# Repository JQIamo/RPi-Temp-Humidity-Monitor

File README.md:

# RPi-Temp-Humidity-Monitor
Raspberry-Pi driven temperature and humidity sensing via DHT22.

Short-URL: http://git.io/vRFkn

## Ordering Boards:
v1.1 Boards are orderable from OSHPark at the following links:

- [PiTempLoggerv1.1-PiSide](https://oshpark.com/shared_projects/A5WHpdao) @ $34.50 per 3 boards
- [PiTempLoggerv1.1-Sensor](https://oshpark.com/shared_projects/NIQoCTse) @ $12.00 per 3 boards

They have been prototyped on a local board-fab machine, and a first run is en-route to the JQI.

## Other needed parts:
For one sensor baord:
- 1 DHT22 [from Adafruit?](https://www.adafruit.com/product/385)
- 1 of the above PiTempLoggerv1.1-Sensor
- 1 of 1-10k 1206 SMT resistor (use a lower resistance, e.g. 1-2k, if your ethernet cable is over 15 feet)
- 1 of 100nf 1206 SMT capacitor
- 1 of ethernet jack (Man. Part No. 555164-1, TE/Amp, get from any distributor)
- 1 Ethernet cable to connect to RPi (whatever length you need)

Per pi:
- 1 of the above PiTempLoggerv1.1-PiSide
- 8 of ethernet jack (Man. Part No. 555164-1, TE/Amp, get from any distributor)
- 1 of 26-pin 2x13 header
- 1 ribbon cable, either:
  - 26 pin
  - 40 pin
  - "Downgrade" cable [from Adafruit](https://www.adafruit.com/products/1986) <-Could also be made yourself with ribbon or connector
- 1 ethernet cable for network access

## Installing on a Raspberry Pi
See instructions in `INSTALL.md`

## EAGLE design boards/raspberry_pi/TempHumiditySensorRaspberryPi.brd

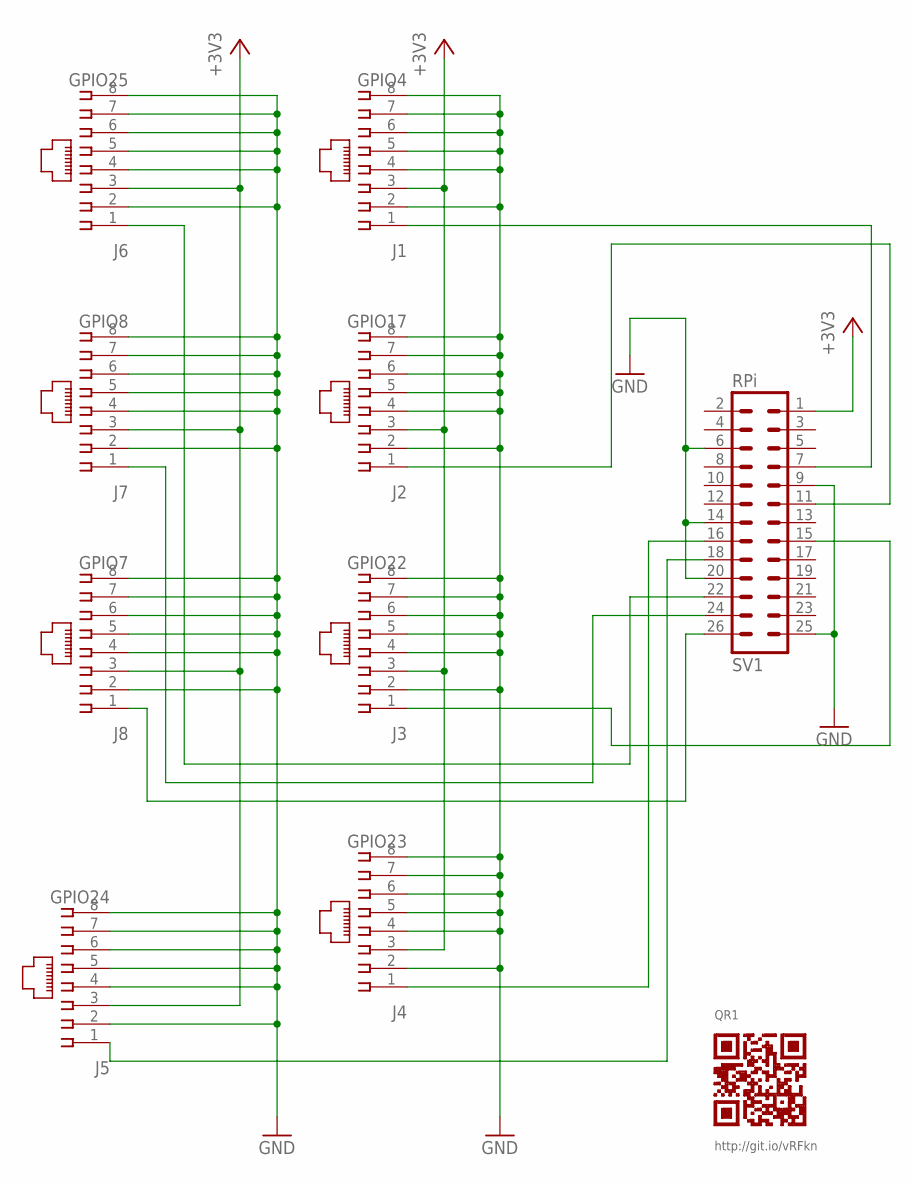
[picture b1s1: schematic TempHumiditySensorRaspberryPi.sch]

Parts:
J1: GPIO4; 555164-1; PARTNO 5555164-1
J2: GPIO17; 555164-1; PARTNO 5555164-1
J3: GPIO22; 555164-1; PARTNO 5555164-1
J4: GPIO23; 555164-1; PARTNO 5555164-1
J5: GPIO24; 555164-1; PARTNO 5555164-1
J6: GPIO25; 555164-1; PARTNO 5555164-1
J7: GPIO8; 555164-1; PARTNO 5555164-1
J8: GPIO7; 555164-1; PARTNO 5555164-1
QR1: QR-HTTP://GIT.IO/VRFKN
SV1: RPi; ML26; PARTNO SBH11-PBPC-D13-ST-BK

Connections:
+3V3: J1.3, J2.3, J3.3, J4.3, J5.3, J6.3, J7.3, J8.3, SV1.1
GND: J1.2, J1.4, J1.5, J1.6, J1.7, J1.8, J2.2, J2.4, J2.5, J2.6, J2.7, J2.8, J3.2, J3.4, J3.5, J3.6, J3.7, J3.8, J4.2, J4.4, J4.5, J4.6, J4.7, J4.8, J5.2, J5.4, J5.5, J5.6, J5.7, J5.8, J6.2, J6.4, J6.5, J6.6, J6.7, J6.8, J7.2, J7.4, J7.5, J7.6, J7.7, J7.8, J8.2, J8.4, J8.5, J8.6, J8.7, J8.8, SV1.6, SV1.9, SV1.14, SV1.20, SV1.25
unnamed: J1.1, SV1.7
unnamed: J8.1, SV1.26
unnamed: J2.1, SV1.11
unnamed: J3.1, SV1.15
unnamed: J4.1, SV1.16
unnamed: J6.1, SV1.22
unnamed: J7.1, SV1.24
unnamed: J5.1, SV1.18

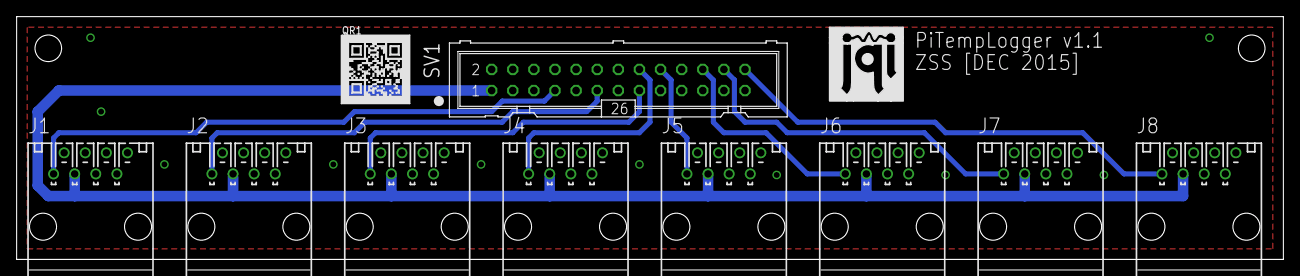
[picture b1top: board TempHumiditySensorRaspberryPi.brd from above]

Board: 2 copper layers, 152.4 x 29.2 mm, 11 parts (0 on the bottom side), 10 nets.

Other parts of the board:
LOGO1: JQI-LOGOSILK; JQI_LOGO_NEGATIVE-SILKSCREEN

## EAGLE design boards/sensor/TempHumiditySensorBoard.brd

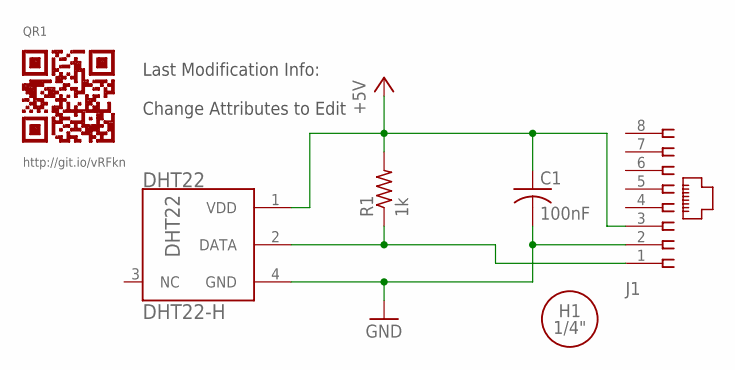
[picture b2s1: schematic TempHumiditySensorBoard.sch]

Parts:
C1: 100nF; C1206; PARTNO CL31B104JBCNNNC
DHT22: DHT22-H; PARTNO 385
H1: MOUNT-HOLE-1/4"-FREE
J1: 555164-1; PARTNO 555164-1
QR1: QR-HTTP://GIT.IO/VRFKN
R1: 1k; R1206; PARTNO ERJ-8ENF2001V
U$2: INFOROW; INIT_DATE_LINE

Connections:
+5V: C1.1, DHT22.1 (VDD), J1.3, R1.2
DATA: DHT22.2 (DATA), J1.1, R1.1
GND: C1.2, DHT22.4 (GND), J1.2

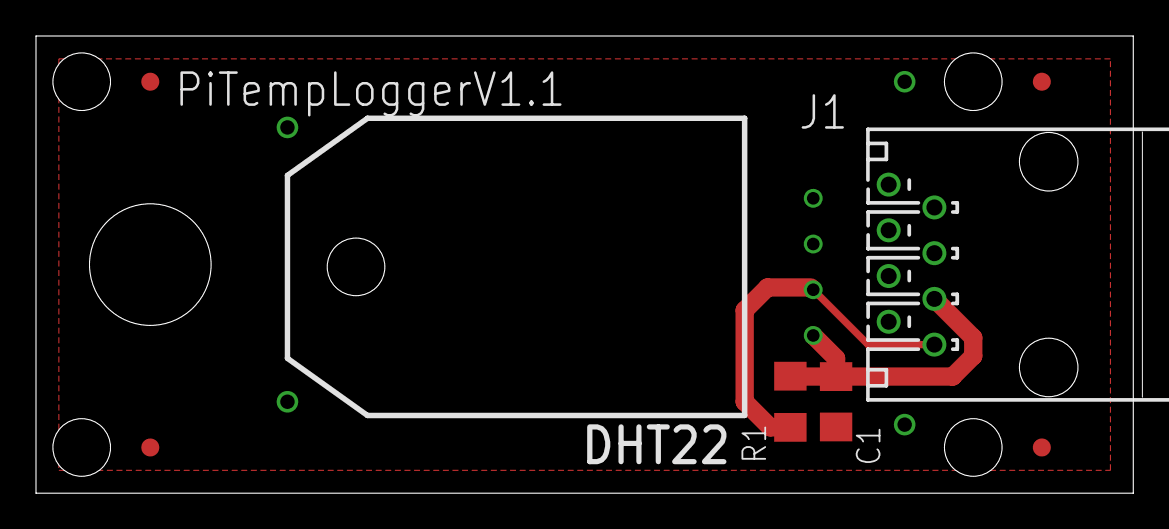
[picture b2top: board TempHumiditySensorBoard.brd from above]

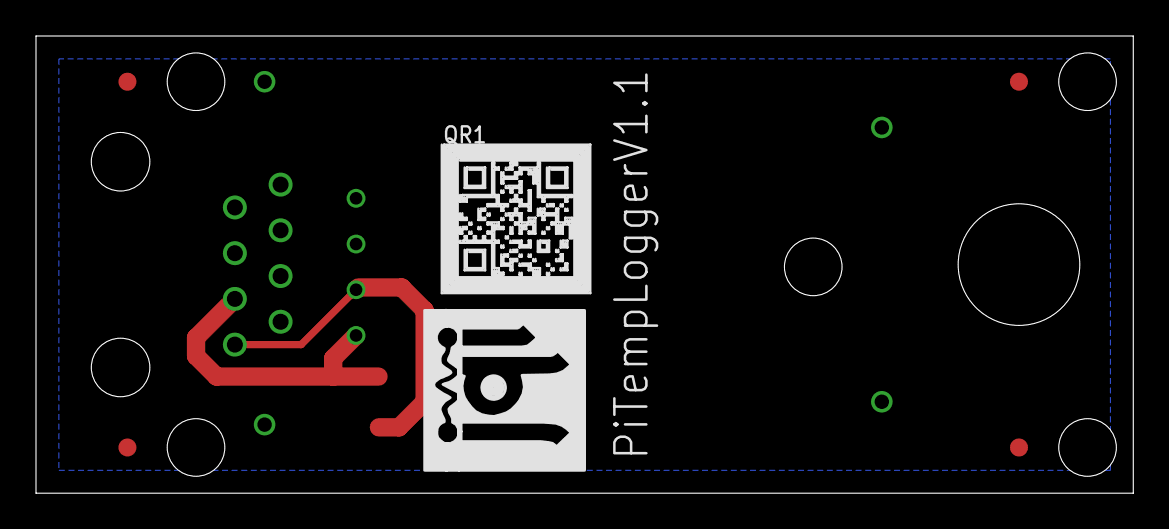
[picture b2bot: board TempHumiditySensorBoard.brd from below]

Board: 2 copper layers, 61.0 x 25.4 mm, 12 parts (3 on the bottom side), 3 nets.

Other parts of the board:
U$1, U$3, U$4, U$5: FID1MM
U$6: JQI_LOGO_NEGATIVE-SILKSCREEN

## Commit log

2015-12-09 Update README.md
    Add git.io URL
2015-12-16 Add QR-Code part library
2015-12-16 Add Raspberry Pi interface board
2015-12-16 Add Sensor Board
2015-12-16 Update README with ordering info
2015-12-16 Add scripts to handle actual logging to influxdb
    readInfluxTemp.py:
    - Handles one-time reading of sensors
    - Attempts to post readings to an influxdb
    - If posting fails, stores to a temporary location for possible
    recovery
    uploadMissedTemps:
2015-12-16 QR Code appears on schematic, has 'QR' identifier
2015-12-16 Work with different board versions
    Multiple versions of the board exists that have different pin<->channel
    mappings. Added:
    - Ability to spec. board version in the configuration file
    - Ability to override pin on a channel-by-channel basis from
    configuration file
    - Default pin-maps in the sensor-reading script.
2016-05-09 Add rough BOM to README.md
    Added BOM sources from an old email to Varun. Should be helpful.
2016-06-09 Add files via upload
    uploaded cad file for the plastic case used for the temp monitor
2016-06-09 Delete RPi-Tempmonitorcase.STL
    Uploading a newer version of the file
2016-06-09 CAD file for the RPi temp monitor's plastic case
2016-06-09 CAD file for the sensor board's plastic case
2016-06-24 update the resistance of the pull-up resistor
    lowering the resistance of the pull-up; the sensor with a 10k resistor does not work for distances greater than 15 feet
2018-05-16 MacroFab files and BOM
    Added BOMs for use with eagle-config and production files for MacroFab.
    DSB
